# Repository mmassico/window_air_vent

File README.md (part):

# Window vent

A demand-controlled window ventilator for one room. Two 80 mm fans move air through a foam window insert: one brings fresh air in, the other exhausts stale air. A single butterfly-damper housing closes both holes with one shaft, turned by a silent stepper motor. An ESP32 reads a CO₂ sensor and runs the fans and the damper.

There is no heat recovery: every litre of air exhausted is lost heat. In exchange it is simple, cheap and automatic. See the estimates below.

> **Status: prototype, running in a window.** The complete unit is installed in a window, on the controller PCB and the [web application](firmware/README.md#the-web-application-webui), and ventilates on its own from its CO₂ reading. It closes when it's loud outside, using a microphone listening through a tube in the foam. Every printed part has been printed and test-fitted (housing, discs, motor plate, magnet cap, electronics box, tube spacer, louvers), and several were refined from those prints: the shaft holes' sacrificial fins, the box's back tabs, the louvers' snap-in combs, and the discs' seats. The lip seals are installed and tested: with the 1.6 mm neoprene, the closed discs now press evenly on the foam all round, after two rounds of tuning the discs' seats (the housing stayed as printed). The housing was then reprinted with flat shaft bosses and the discs with matching flats: the gap at the bosses is gone (the first, curved bosses left 0.3 to 0.75 mm), and the reprinted electronics box fits too, its back tabs and the notches for the fan's rubber bumpers included; the tabs make mounting it on the housing much easier. The shaft holes' sacrificial fins work as intended: no warping, and they drill out easily. The lip foam cutting guides are printed and tested: cutting the foam with them is much easier, faster and more accurate than with the paper templates. The foam-free `disc_nofoam` is checked in CAD but not tested yet. Its CO₂ reading agrees with a calibrated meter within the sensor's tolerance. What's still to come is time: it has only just gone in, so it hasn't seen a season yet. The geometry is also checked in CAD (closed solids, the discs swing freely, the lips stop them).

## How it works

- **Foam insert.** A block of 2 in (51 mm) XPS foam, 30 psi grade, fills the window gap (100 mm or less, so a child can't fit through). Two 83 mm holes (a 3-1/4 in hole saw, see [drilling](#drilling-the-foam-insert)), stacked vertically: exhaust on top, intake below. The cold incoming air sinks, and the warm exhaust rises, so with the intake low neither one loops straight back into the other, indoors or out. An [insect screen](#insect-screen) in a printed frame covers the outdoor face.
- **Damper housing.** It sits on the **room** face of the foam, so its moving parts stay warm and dry (no ice). Its two spigots fit snugly in the foam holes; two O-rings on each are optional, for a hole that comes out loose. The housing comes out in spring, and the foam insert stays reusable.
- **Butterfly dampers.** One vertical 5 mm steel shaft runs through both ducts and carries a disc in each. A quarter turn opens or closes both. Each disc closes against two half-ring lips lined with thin foam (or bare, with [`disc_nofoam`](#without-lip-foam)), one on each side of the shaft. One lip is flat; the other is a 45° cone, and the half of the disc that closes against it (engraved B) has a matching 45° bevel, so neither prints as a flat overhang.
- **Motor and encoder.** A NEMA 17 pancake stepper on top turns the shaft through a flexible coupler. A TMC2209 driver keeps it silent. The motor screws to a separate plate on the bench, and the plate then screws onto a frame on top of the housing from above. An AS5600 magnetic encoder at the bottom reads the absolute shaft angle, so the firmware always knows whether the dampers are really closed, with no homing and no limit switch.
- **Fans.** Two 80 mm PWM fans screw onto the room end of the housing.
- **Electronics box.** A tray under the housing holds a 5 × 7 cm perfboard with the ESP32 and the TMC2209 soldered on. The encoder plate is its lid, and its front wall rises to close the front of the bottom bay. The cables run down the right side (seen from the room), hidden behind the fans and held by three tie-wrap anchors on the back of the fan plate; the same anchors and a cable entry on the left side allow the mirror image. Power comes from two plug-in adapters: a 12 V brick for the fans and the motor, whose wire comes in with the other cables, and a 5 V USB-C adapter for the ESP32, whose cable passes through a diamond opening in the left wall. The [layout drawing](doc/ebox_layout.svg) shows where everything goes on the perfboard.
- **Water stays out of the room.** A 3 mm drip dam across the lower part of each bore, just before the fan, stops droplets from running indoors. Around the bottom shaft hole in each duct, a 16 mm boss rises 3 mm above the floor, so water flows around it instead of down the shaft. An optional [drip tray](#drip-tray) under the unit, on the window ledge, catches anything that still drips; it evaporates there.
- **How it seals.** The lips do the sealing, not the gap between the disc and the bore: the flat lip is 5.6 mm wide and overlaps the disc edge by 2 mm, and the conical lip meets the disc's bevelled rim over a band about 2.8 mm wide (the same 2 mm across the bore, along the 45° slope). Between them is 1.6 mm neoprene in a gap of about 1.5 mm, so it is only lightly squeezed: the disc's two seats are relieved for it (see [cutting the lip foam](#cutting-the-lip-foam)). The disc is 67 mm in a 74 mm bore so it can be slid in edge-on past the dam and the bosses. Around the shaft, where the lips must stop to clear the hub, a boss at the top and the one at the bottom close the gap. Their inner faces are flat, square to the shaft, and the disc's two shaft ends are cut to matching flats: a flat end turning about the shaft stays in its own plane, so the gap is 0.2 mm at every angle.

## Estimates (one sleeper)

| Airflow (each way) | CO₂ in the room | Heat lost at −20 °C outdoors |
|---|---|---|
| 5 L/s (11 CFM) | ~1000 ppm | ~250 W |
| 8 L/s (17 CFM) | ~800 ppm | ~400 W |
| 11 L/s (23 CFM) | ~700 ppm | ~540 W |

At 8 L/s, roughly 10 hours a day over a cold-climate heating season (about 200 days, electricity at 7–11 ¢/kWh), the lost heat costs about $35–45. The fans use about 1 W each.

## Printed parts

| Part | <div style="width:180px">Thumbnail</div> | Qty | Description | Size (mm) | Print orientation |
|---|:---:|---|---|---|---|
| `body` |  | 1 | Housing: two ducts with the damper lips, drip dams and shaft bosses, spigots for the foam, fan plate, motor frame and encoder plate | 90 × 241 × 114 | Fan plate on the bed, no supports |
| `disc` |  | 2 | Butterfly damper disc, clamped to the shaft by two M3 grub screws; the half engraved B has a 45° bevel on its rim. Its seats are relieved for the 1.6 mm lip foam, and its two shaft ends are cut flat to face the bosses | 67 × 65 × 14 | Plate on the bed, hub up |
| `disc_nofoam` |  | (2) | Instead of `disc`, for lips [without foam](#without-lip-foam): half A is 3.6 mm thick and half B's bevel is smaller, so both seats close to 0.3 mm from the bare lips | 67 × 65 × 14 | Plate on the bed, hub up |
| `motor_plate` |  | 1 | The motor screws to it on the bench; it then sits on top of the housing: two screws in front of the motor, and two tabs at the back, down through the frame and screwed to the tower walls | 56 × 61 × 15 | Top face on the bed, tabs up |
| `magnet_cap` |  | 1 | Holds the encoder magnet on the bottom end of the shaft; one M3 grub screw, height adjustable ±1 mm | 14 × 14 × 12 | Bore down |
| `ebox` |  | 1 | Electronics box under the housing; its front wall also covers the front of the bottom bay, and two back tabs screw to the bay walls | 80 × 76 × 64 | Floor on the bed |
| `tube_spacer` |  | 1 | Flat "8" over both spigots, against the stop rings and squeezed by the foam: it holds the spigots' ends at their spacing, so foam holes slightly off 96 mm can't bend the ducts and bind the shaft. The vent sits 2.5 mm further out of the foam | 90 × 186 × 2.5 | Flat |
| `screen_frame` |  | 1 | [Insect screen](#insect-screen) frame on the foam's outdoor face: the mesh is pressed into a groove around both holes, two sleeves plug into the holes, four screws in the corners, a drain at the bottom of each hole | 94 × 193 × 15 | Outdoor face on the bed, sleeves up |
| `tray` |  | (1) | Optional [drip tray](#drip-tray) on the window ledge, under the whole unit: the electronics box stands on ribs above its floor, and an adjustable leg in each corner levels it | 112 × 115 × 22 | Floor on the bed |
| `tray_feet` |  | (4) | The tray's feet, one per leg: each slides in its post's socket, carries a captive M3 nut, and has a groove for the M2 stop | 9 × 9 × 20 each | On its side, the nut's slot up |

**Housing and discs must match.** The housing's shaft bosses have flat inner faces, and the discs have matching flats. A housing printed before this change (curved boss faces) needs the earlier discs: set `flat_boss = false` in `cad/window_vent.scad` and export `disc` (or `disc_nofoam`). A disc with flats leaves a 1.6 mm gap at a curved boss, and a disc without them won't turn between flat bosses.

**For a 180 mm printer** (e.g. Bambu Lab A1 mini), print the housing in two halves instead of `body`. The cut runs midway between the two ducts, where only the fan plate joins them; a small splice plate behind the fan plate joins the halves again with four M3 screws, driven from the fan side in the band between the two fans. Each half prints like the full housing, in about half the time (roughly 5–6 h), so they can go on different days; use the same spool and profile for both.

| Part | <div style="width:180px">Thumbnail</div> | Qty | Description | Size (mm) | Print orientation |
|---|:---:|---|---|---|---|
| `body_top` |  | 1 | Upper half: exhaust duct, upper fan, motor frame, and both middle tie-wrap anchors (whole) | 90 × 130 × 114 | Fan plate on the bed, no supports |
| `body_bottom` |  | 1 | Lower half: intake duct, lower fan, encoder plate; notched under the two middle anchors | 90 × 116 × 114 | Fan plate on the bed, no supports |
| `splice` |  | 1 | Joins the halves behind the fan plate; four M3 nut pockets on its back | 60 × 32 × 6 | Flat, nut pockets up |

**Optional test prints, before the housing.** Print the small real parts first (discs, motor plate, magnet cap, about 1.5–2 h): they test the rod, the grub screws, the motor and the magnet. Then:

| Part | <div style="width:180px">Thumbnail</div> | Size (mm) | Time | What it tests |
|---|:---:|---|---|---|
| `fittest` |  | 60 × 34 × 22 | about 20–30 min | The housing's printer-sensitive features, in its print orientation, engraved A to G (see below) |
| `oring_test` |  | Ø 90 × 18 | about 30 min | One spigot section (with an O-ring groove): push it into a test hole cut in a foam scrap, bare first; if it's loose, try it with an O-ring |

**The fit-test coupon.** It copies seven features of the housing that depend most on the printer: holes and a slot, a nut pocket, a pilot for self-tapping screws, the conical lip's 45° ledge and a countersink. Each is engraved with a letter, A to G. Print it with the housing's filament and settings, then check each feature against the table below: if one fails, adjust the slicer (or the hole sizes in the model) before starting the 9–12 hour housing print.

| | Feature | Copied from | Pass if |
|---|---|---|---|
| A | M3 hole + nut pocket | fan plate | the nut drops in and stays; an M3 screw passes freely |
| B | Ø 2.5 self-tapping pilot | the box cover bosses | an M3 screw cuts a firm thread without splitting the post |
| C | 5.6 mm ledge with a 45° underside (on the back of the plate) | conical lip B in each bore | the slope is smooth, not drooping or stringy |
| D | Ø 5.4 shaft hole, horizontal, with its sacrificial fin | bearing holes in the duct walls | the top of the hole stays round; after drilling the fin out (see below), the 5 mm rod turns freely |
| E | AS5600 diagonal slot (3.5 wide) on a 2 mm standoff | encoder plate | an M3 screw passes at both ends of the slot |
| F | M3 hole, horizontal | motor frame | an M3 screw passes freely |
| G | M3 hole with a 90° countersink, opening on the bed | split housing joint (`body_top` and `body_bottom`) | an M3 flat-head screw sits flush or just below the surface |

PETG. No support is needed anywhere: every face that looks down when printing (the lip B seat, the disc bevel, the boss sides, the O-ring grooves, the countersinks) slopes at 45° or less.

### Filament

About **0.5 kg of PETG** for one unit (about half a 1 kg spool), or roughly $12–17 at $25–35/kg.

| Part | Qty | Solid volume |
|---|---|---|
| `body` | 1 | 282 cm³ |
| `disc` | 2 | 2 × 12.7 = 25 cm³ (`disc_nofoam`: 2 × 14.7) |
| `motor_plate` | 1 | 12.6 cm³ |
| `magnet_cap` | 1 | 1.6 cm³ |
| `ebox` | 1 | 47 cm³ |
| `tube_spacer` | 1 | 4.5 cm³ |
| `screen_frame` | 1 | 39 cm³ |
| **Total** | | **≈ 412 cm³** |

The split housing (`body_top` 136 cm³, `body_bottom` 145 cm³, `splice` 8 cm³) adds about 7 cm³ (9 g).

- Printed fully solid, 412 cm³ of PETG (1.27 g/cm³) weighs about 523 g.
- Infill hardly matters: almost every wall, plate, lip and disc is 6 mm thick or less, so with 4–6 perimeters the slicer prints it solid anyway. Expect about 470–520 g, plus a little for the skirt or brim and purging.
- The optional test prints add about 35 cm³ (44 g): `fittest` 12 cm³, `oring_test` 20 cm³, `fin_test` 3 cm³. The optional `drill_guide` adds 9 cm³ (11 g), and the optional lip foam cutting guides 9 cm³ (12 g): `foam_guide_a` 4.3 cm³, `foam_guide_b` 5.0 cm³. The screen frame's `screen_test` adds 6 cm³ (7 g). The optional drip tray adds 46 cm³ (58 g): `tray` 41 cm³, `tray_feet` 5 cm³, and its `tray_test` 5 cm³ (6 g).
- Print time: very roughly 9–12 hours for the housing on a Bambu Lab P1 (0.2 mm layers; about 7–9 hours at 0.28 mm), and about 3–4 hours for all the other parts together. The slicer gives the exact figures.

### Slicer settings

Most parts are thin, so the number of walls (Bambu Studio: Strength → **Wall loops**) matters more than the infill percentage: with enough walls, the thin parts come out solid and the infill only fills the few thicker zones.

| Part | Wall loops | Sparse infill | Why |
|---|---|---|---|
| `body` (or `body_top` and `body_bottom`) | 4 | 25 % | Thin walls everywhere; the infill only reaches the thick zones (bosses, spigot roots, fan plate). No supports: a sacrificial fin holds up the top of each of its four shaft holes (see below) |
| `disc` (or `disc_nofoam`) | 5 | 40 % | The grub screws thread into the hub: 5 loops leave about 2 mm of solid plastic around each hole |
| `motor_plate` | 5 | 40 % | Screw holes, bosses and tabs under clamping load |
| `magnet_cap` | | 100 % | Tiny, with a grub screw in it: print it solid |
| `splice` | 5 | 40 % | Joins the two halves: nut pockets and countersunk screws |
| `ebox` | 4 | 15–20 % | No real loads; a 4th wall (same print time) makes the walls around the screw holes stronger |
| `tube_spacer` | | 100 % | Thin rings (3 mm wide, 2.5 mm thick) that must not stretch: print it solid |
| `screen_frame`, `screen_test` | 4 | 25 % | Thin plate and sleeves: 4 walls print them nearly solid, so the groove's walls hold the spline |
| `tray`, `tray_feet`, `tray_test` | 4 | 25 % | The 5 bottom layers below keep the tray's 1.6 mm floor watertight; 4 walls make the posts and feet nearly solid |
| `fittest`, `oring_test` | 4 | 25 % | As the housing, so they test what the housing will be |
| `drill_guide` | 4 | 40 % | Small; 4 walls make the bushings solid |
| `foam_guide_a`, `foam_guide_b` | 4 | 40 % | Thin plate and rib: 4 walls print them solid, so they stay flat and stiff |
| `louver_chassis` | 3 | 20 % | Light load |
| `louver_blade` | 3 | 15 % | Thin and light; their pins come out solid anyway |
| `louver_link_nopad` (or `louver_link`), `louver_retainer` | | 100 % | Small and thin |
| `fan_spacer` | 3 | 15 % | Thin vertical walls and vanes: 3 walls print them solid |
| `fan_shim` | | 100 % | Thin sheet, 1.25 mm: print it solid, at a layer height that gives that thickness |
| `fan_gasket_template` | 3 | 15 % | Just a template |

- **Infill pattern: gyroid.** Equally strong in every direction, and it prints smoothly in PETG.
- **Top and bottom shell layers: 5.** Flat faces stay smooth and the infill doesn't show through.
- **Supports: none.** Every part is designed to print without them. The housing's four shaft holes print horizontal, so each one carries a sacrificial fin: a thin lattice of X's (0.8 mm, two nozzle lines; `fin_t` in the model, 0 for none) standing on the bottom of the hole and holding up its top, with 1.5 mm clear at each end. After printing, drill the fins out by hand with a 5.2 mm bit (13/64 in, the one used on the housing; 5.4 or 5.5 mm also works): the bit enters the clear end first, sits square, and cuts the fin easily. Tested on the housing: the holes come out round, with no warping, and the 5 mm rod turns freely. Feature D of `fittest` is the same hole with the same fin, and `fin_test` is a 10-minute block with two of them.

## Hardware

Prices: Amazon.ca, October 2026, before taxes. Packs of two leave a spare.

| Item | Qty | Notes | Price (CAD) |
|---|---|---|---|
| 80 mm PWM fan, ≥ 2 mm H₂O static pressure | 2 | Noctua NF-A8 PWM (2.37 mm H₂O, 17.7 dB(A) max). Run at 30–60% | 2 × $24.95 |
| Stepper motor, NEMA 17 pancake | 1 | StepperOnline 17HS08-1004S (42 × 42 × 20 mm, 5 mm shaft, 13 N·cm). Any NEMA 17 fits the mount | $26.50 |
| TMC2209 stepper driver | 1 | StealthChop for silent moves; UART for StallGuard | $16.99 (pack of 2) |
| AS5600 magnetic encoder board + **diametric** magnet | 1 | Sold with the magnet (the kit: 23.3 × 22.8 mm board, 3.95 × 2 mm magnet). A 20 × 20 board with 15 mm hole spacing also fits: 4 × M3 × 12 + nuts onto standoff pads on the bottom plate. See the magnet note below | $12.69 (pack of 2) |
| ESP32-S3 dev board | 1 | An ESP32-S3-N16R8 board in the DevKitC-1 layout (2 × 22 pins) with a U.FL connector and an external antenna, for the v2.0 PCB; or the Freenove ESP32-S3-WROOM Lite (FNK0099), the board the firmware's pinout was first written for, which also fits the v2.0 PCB on its 20 inner pins of each row. Other ESP32-S3-WROOM-1 boards work with a pin check. Flash it over USB on the bench; the final firmware updates over Wi-Fi | — |
| CO₂ sensor, NDIR | 1 | Sensirion SCD40 module (CO₂ + temperature + humidity, I²C). Not CCS811/SGP30 ("eCO₂" estimates) | $37.45 |
| DS18B20 temperature probe, waterproof | 1 (+1 optional) | Outdoor air: the 6 mm stainless probe on its cable goes through the foam insert ([template](#drilling-the-foam-insert)); if possible, far from the exhaust (the upper hole), whose warm air skews the reading. A second one, indoors on an inside wall, is optional: the SCD40 already reads the room's temperature | — |
| Steel rod, 5 mm × 200 mm | 1 | Damper shaft. 200 mm fits as is, no cutting. If it is HSS (very hard), grind a small flat with a rotary tool where each disc and the coupler clamp, so the screws can't slip | $12.79 (pack of 2) |
| Flexible shaft coupler, 5–5 mm, 19 × 25 mm | 1 | | $13.49 (pack of 2) |
| M3 × 35 screws + M3 nuts | 8 each | Fans. Two stacked fans per duct ([optional](#optional-two-fans-per-duct-with-a-spacer)): M3 × 75 with the `fan_spacer` and its shims, M3 × 60 without | — |
| M3 × 8 screws | 4 | Motor to motor plate, through the bosses under the plate. Not longer: the motor's holes are only 2.5 mm deep ([section](doc/motor_mount.svg)) | — |
| M3 × 10 (or M3 × 12) screws + M3 nuts | 6 each | Motor plate: two through the frame in front of the motor, two through the tower walls and the plate's back tabs. Electronics box: two through the bay walls and the box's back tabs | — |
| M3 grub screws, 6 mm (and one 4–5 mm) | 5 | Two 6 mm per disc, 24 mm apart along the hub, so the disc can't rock on the shaft (flush with the hub); one 4–5 mm in the magnet cap (a 6 mm one would stick out 1.5 mm). Self-tapping into the plastic | — |
| O-rings, 74 × 3 mm, nitrile 70A | 4 | Optional, and not needed by default: the plain Ø 83.7 spigots are a snug fit in the hole (83.3 mm with the 3-1/4 in hole saw). For a hole that comes out loose, set `orings = true` before printing the housing: two grooves per spigot, sized for this O-ring (about 6% stretch, 20% squeeze in an 83.3 mm hole) | $12.79 (pack of 10) |
| Insect screen kit: fibreglass mesh, 0.125 in screen spline, spline roller | 1 | [Insect screen](#insect-screen): a piece of mesh about 115 × 210 mm and about 50 cm of spline (or 3 mm O-ring cord, cut from the 74 × 3 O-rings above) | — |
| Countersunk screws, 8 mm head (3.5 mm high), about 25 mm long | 4 | Screen frame into the foam (4.25 mm holes) | — |
| M3 × 20 button head screws (ISO 7380, 2 mm hex) + M3 nuts | 4 each | Optional [drip tray](#drip-tray): the legs. Felt pads under the feet are optional too | — |
| M2 × 6 flat head screws | 4 | Optional [drip tray](#drip-tray): the legs' stops, through each post's outer wall (self-tapping) | — |
| XPS foam board, 2 in (51 mm), 30 psi | 1 | Foam insert, e.g. Owens Corning FOAMULAR C-300 (2 × 24 × 96 in, R-10). The 30 psi grade over the 20 psi (wall) one: stiffer under the housing's weight, it doesn't creep around the spigots, and the hole saw cuts it cleaner. Many boards have shiplap (SL) edges, stepped to overlap on a wall: cut the insert from the middle of the board, or saw the step off any edge that meets the window frame | — |
| Closed-cell neoprene foam sheet, self-adhesive, 1/16 in (1.6 mm) | 1 | Lip seals, cut with the [templates](#cutting-the-lip-foam); not needed with `disc_nofoam` ([without lip foam](#without-lip-foam)). The model leaves a 1.5 mm gap, so the foam is only lightly squeezed: closed-cell neoprene is too stiff for more | |
| Perfboard (protoboard), 5 × 7 cm, holes 66 × 46 mm | 1 | Carrier for the ESP32 and the TMC2209 in the electronics box | |
| Resistors and capacitor for the perfboard | | 1 kΩ (TMC2209 UART), 10 kΩ × 5 (driver enable pull-up, two fan PWM pull-downs, two tach pull-ups), 100 kΩ + 22 kΩ (12 V sense), 4.7 kΩ (DS18B20 pull-up; × 2 with the optional indoor sensor), 100 µF ≥ 25 V electrolytic (TMC2209 motor supply). See [firmware/README.md](firmware/README.md) | — |
| Female pin headers, 2.54 mm (optional) | to suit | Sockets for the ESP32 and the TMC2209 instead of soldering them, so they unplug for replacement (`esp_mount`, `tmc_mount`; the box has room for both) | |
| M2 screws, about 6 mm | 4 | Perfboard onto the box standoffs (self-tapping) | |
| M3 × 12 countersunk (flat head, ISO 10642 or DIN 965) screws + M3 nuts | 4 each | Split housing only: fan plate to the splice, heads flush in 90° countersinks | — |
| M3 × 12 screws | 2 | Electronics box: through the front cover (self-tapping) | — |
| Small tie wraps, 2.5–3.6 mm | 3+ | Cable anchors (three on each side; use one side) | |
| 12 V power brick | 1 | Fans and motor, about 1 A. Only its wire enters the box, to a 2-pin screw terminal on the perfboard | — |
| USB-C power adapter, 5 V (1 A or more), and a USB-C cable | 1 | Powers the ESP32 through its USB-UART connector, which also gives the console. The cable passes through a diamond opening in the box's left or right wall (`usb_port`: or only a cross to drill, or nothing; `usb_side`: left, right or both) | — |
| **Total bought** | | Not counting the foam insert and foam sheet, or the two power adapters | **≈ $181** |

### The stepper motor

The StepperOnline 17HS08-1004S, from its sheet and checked with a caliper. Its M3 holes are only 2.5 mm deep, so the motor plate has a 2 mm boss under each screw hole: through the 4 mm plate and the boss, an M3 × 8 reaches 2 mm into the motor. The bosses and the screw heads sit in the frame's diamond pockets.

Its four leads, from the sheet, and where they go on the controller PCB's motor header J4 (silkscreen 1A, 1B, 2A, 2B; the TMC2209's M1A, M1B, M2A, M2B). Each coil is a pair: about 3.7 Ω between its two leads, nothing between the pairs, which an ohmmeter confirms before plugging in.

| J4 pin | Silkscreen | Driver output | Lead | Coil |
|---|---|---|---|---|
| 1 (square pad) | 1A | M1A | Black | A |
| 2 | 1B | M1B | Green | A\ |
| 3 | 2A | M2A | Red | B |
| 4 | 2B | M2B | Blue | B\ |

If the motor turns the wrong way, swap the two leads of one coil (black and green, for example). Never plug or unplug the motor with 12 V on: it can destroy the driver.

### The AS5600 board, a magnetic rotary position sensor

The kit board, measured. Its four mounting holes form a 16.7 × 16.2 mm rectangle (not a square); the diagonal slots in the encoder plate take it as well as the smaller 20 × 20 boards. Mount it chip up, under the magnet, and solder the wires straight into its holes: they run inward under the board, in the 2 mm the standoff pads leave, and down through the diamond window under the chip.

### The ESP32-S3 board, the Wi-Fi microcontroller

The Freenove ESP32-S3-WROOM Lite, measured. Its two pin rows are 25.3 mm apart, so they land 10 holes apart on the perfboard. It has two USB-C connectors at one end: plug the cable into the USB-UART one (power and console). The module's antenna sticks out 7 mm beyond the other end.

### The TMC2209 module, a silent stepper motor driver

A StepStick-format driver, measured: 20.81 × 15.08 mm, two rows of 8 pins 12.7 mm apart (5 holes on the perfboard). The chip is on the underside; its heatsink (15 × 14.4 mm, fins along the pin rows) sticks onto the thermal pad on top, toward the DIR/GND end so it clears the potentiometer, and stands 14.70 mm from the board's underside.

Check which pin carries the chip's UART. Some modules, such as the TMC2209-LA, have a 0 Ω link that routes it to either the PDN pin (pin 4) or the UART pin (pin 5), and come with it on PDN; the controller uses both. On the PCB, since v1.3, two 0 Ω 0402 jumpers on the back, JP3 (pin 4) and JP4 (pin 5), put the UART line on both pins, so either kind works; leave one out if a module uses that pin for something else. On an older PCB or the perfboard, nothing else uses pin 4, so a short wire between pins 4 and 5 on the board's underside does the same (the firmware README's bring-up, step 5, shows how to tell).

### The SCD40 board, the CO₂ sensor

The Sensirion SCD40 on a small 13.70 × 21.70 mm board, measured: 7.85 mm from its underside to the sensor's top, four pin holes 2.54 mm apart along the bottom edge (GND, VDD, SCL, SDA). It carries its own I²C pull-ups (R1, R2, 10 kΩ), so the controller needs none for it. On the controller PCB, J5 has the same pin order, so a straight 4-wire cable joins them. Keep the sensor's membrane uncovered (see the warning below).

> [!WARNING]
> **SCD40: do not remove the white membrane on top of the sensor.** It looks like a small sticker, but it is part of the sensor: a gas-permeable filter that lets ambient air reach the photoacoustic NDIR cell while keeping dust, splashes and other contaminants out. Do not press on it, cover it, or clean near it with solvents or compressed air.

### The MAX9814 board, the microphone (optional)

For the [audio mode](firmware/README.md#wiring), measured: 25.6 × 14.3 × 1.62 mm, 9 mm from its underside to the capsule's top, and parts up to about 3 mm on the back. The 9.70 mm capsule sits 2.10 mm from one end, centred across the board; the five header holes (GND, Vdd, Gain, Out, AR) run along the other end, and two mounting holes flank the capsule. Tie Gain to Vdd (40 dB) and leave AR open. It lies capsule down in the [microphone tube](window_insert/README.md#outdoor-microphone).

### The electronics box layout

The box seen from above, to scale, with the room at the bottom. The ESP32 lies across the back half, its pins soldered on the perfboard's grid, with its USB-end pins one column in from the board's edge so they clear the corner standoff; the TMC2209 sits at the front right, next to the 12 V terminal and the cable entry. The ESP32 can also be turned 180° in the same place, USB end toward the right wall: the box has a diamond opening on each side (views `ebox_elec` and `ebox_elec_alt` in the model). Keep wires and copper away from the antenna's end.

### Firmware

The ESP32 runs Arduino sketches (esp32 core 3.x). The first, [`firmware/baremetal/`](firmware/baremetal), is a serial command console that tests each electronic part on its own: fans, motor and driver, encoder, CO₂ sensor, temperature probes and the 12 V supply, and optionally a microphone's sound level (audio mode). The second, [`firmware/webui/`](firmware/webui), is the application: the CO₂ control, with its own web page on the home network for the live readings, graphs, settings and manual control, and a simulation that stands in for the sensors until they're connected. Both compile cleanly, and the web application runs on the bare ESP32 board in simulation, and the bare-metal console has now checked every part on the bench. [firmware/README.md](firmware/README.md) has the board settings, the [wiring diagram](firmware/images/wiring.svg), a part-by-part bring-up, the command list and the web application.

**Building the perfboard.** The [build plan](doc/perfboard.svg) puts this wiring on the 5 × 7 cm protoboard: the ESP32-S3 and the TMC2209 on their grid positions in the box, the headers, resistors, capacitor and 12 V terminal around them, and 61 numbered wires on the underside, each listed with both of its holes. A [PDF version](doc/perfboard.pdf) splits it over three landscape Letter pages for the bench: the component side, the solder side and the wire list. Solder the parts and the wires that run under the modules first, then the two modules.

<p align="center">
  
</p>

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
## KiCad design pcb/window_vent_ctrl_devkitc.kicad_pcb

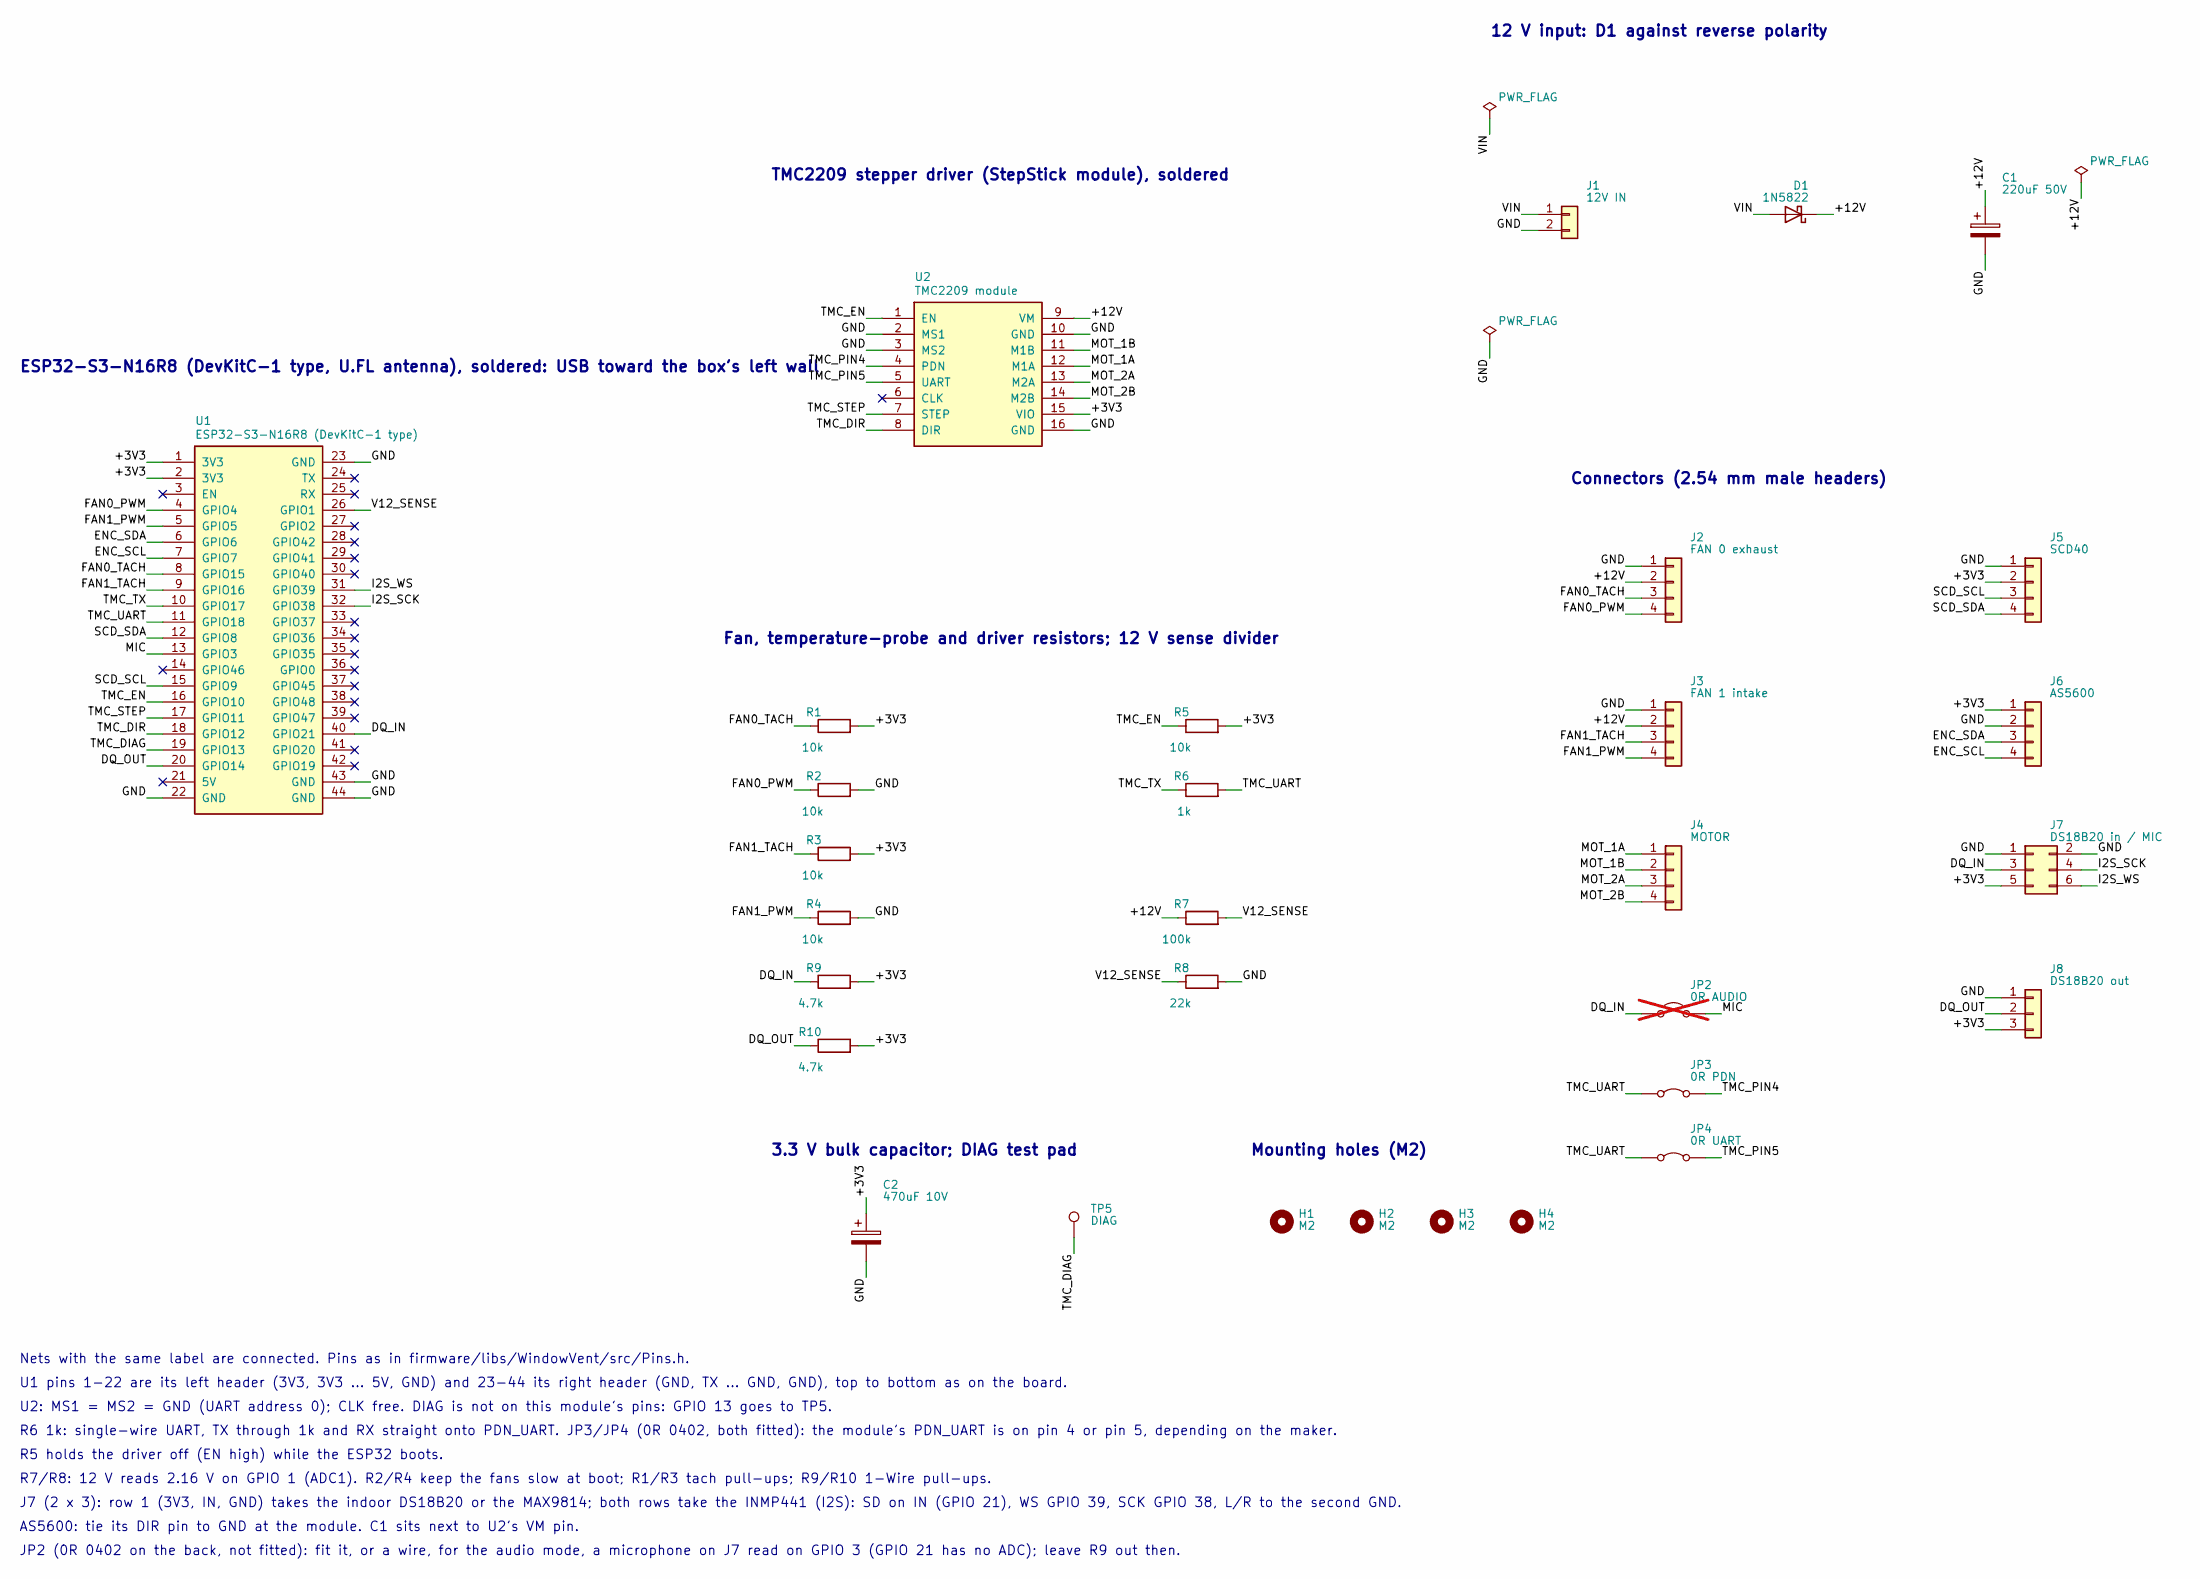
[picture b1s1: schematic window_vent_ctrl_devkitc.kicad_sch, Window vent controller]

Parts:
C1: 220uF 50V; CP_Radial_D10.0mm_P5.00mm
C2: 470uF 10V; CP_Radial_D6.3mm_P2.50mm
D1: 1N5822; D_DO-201AD_P5.08mm_Vertical_AnodeUp_Tight
H1, H2, H3, H4: M2; MountingHole_2.2mm_M2
J1: 12V IN; PinHeader_1x02_P2.54mm_Vertical
J2: FAN 0 exhaust; PinHeader_1x04_P2.54mm_Vertical
J3: FAN 1 intake; PinHeader_1x04_P2.54mm_Vertical
J4: MOTOR; PinHeader_1x04_P2.54mm_Vertical
J5: SCD40; PinHeader_1x04_P2.54mm_Vertical
J6: AS5600; PinHeader_1x04_P2.54mm_Vertical
J7: DS18B20 in / MIC; PinHeader_2x03_P2.54mm_Vertical
J8: DS18B20 out; PinHeader_1x03_P2.54mm_Vertical
JP2: 0R AUDIO; R_0402_1005Metric_Pad0.72x0.64mm_HandSolder; not fitted
JP3: 0R PDN; R_0402_1005Metric_Pad0.72x0.64mm_HandSolder
JP4: 0R UART; R_0402_1005Metric_Pad0.72x0.64mm_HandSolder
R1, R2, R3, R4: 10k; R_Axial_DIN0207_L6.3mm_D2.5mm_P2.54mm_Vertical
R5: 10k; R_DIN0207_P10.16mm_Flat_Tight
R6: 1k; R_DIN0207_P10.16mm_Flat_Tight
R7: 100k; R_DIN0207_P10.16mm_Flat_Tight
R8: 22k; R_DIN0207_P10.16mm_Flat_Tight
R9, R10: 4.7k; R_DIN0207_P10.16mm_Flat_Tight
TP5: DIAG; TestPoint_THTPad_D2.0mm_Drill1.0mm
U1: ESP32-S3-N16R8 (DevKitC-1 type); ESP32S3_DevKitC_N16R8
U2: TMC2209 module; TMC2209_StepStick

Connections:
/+3V3: C2.1, J5.2, J6.1, J7.5, J8.3, R1.2, R3.2, R5.2, R9.2, R10.2, U1.1 (3V3), U1.2 (3V3), U2.15 (VIO)
/+12V: C1.1, D1.1 (K), J2.2, J3.2, R7.1, U2.9 (VM)
/DQ_IN: J7.3, JP2.1 (A), R9.1, U1.40 (GPIO21)
/DQ_OUT: J8.2, R10.1, U1.20 (GPIO14)
/ENC_SCL: J6.4, U1.7 (GPIO7)
/ENC_SDA: J6.3, U1.6 (GPIO6)
/FAN0_PWM: J2.4, R2.1, U1.4 (GPIO4)
/FAN0_TACH: J2.3, R1.1, U1.8 (GPIO15)
/FAN1_PWM: J3.4, R4.1, U1.5 (GPIO5)
/FAN1_TACH: J3.3, R3.1, U1.9 (GPIO16)
/GND: C1.2, C2.2, J1.2, J2.1, J3.1, J5.1, J6.2, J7.1, J7.2, J8.1, R2.2, R4.2, R8.2, U1.22 (GND), U1.23 (GND), U1.43 (GND), U1.44 (GND), U2.2 (MS1), U2.3 (MS2), U2.10 (GND), U2.16 (GND)
/I2S_SCK: J7.4, U1.32 (GPIO38)
/I2S_WS: J7.6, U1.31 (GPIO39)
/MIC: JP2.2 (B), U1.13 (GPIO3)
/MOT_1A: J4.1, U2.12 (M1A)
/MOT_1B: J4.2, U2.11 (M1B)
/MOT_2A: J4.3, U2.13 (M2A)
/MOT_2B: J4.4, U2.14 (M2B)
/SCD_SCL: J5.3, U1.15 (GPIO9)
/SCD_SDA: J5.4, U1.12 (GPIO8)
/TMC_DIAG: TP5.1, U1.19 (GPIO13)
/TMC_DIR: U1.18 (GPIO12), U2.8 (DIR)
/TMC_EN: R5.1, U1.16 (GPIO10), U2.1 (EN)
/TMC_PIN4: JP3.2 (B), U2.4 (PDN)
/TMC_PIN5: JP4.2 (B), U2.5 (UART)
/TMC_STEP: U1.17 (GPIO11), U2.7 (STEP)
/TMC_TX: R6.1, U1.10 (GPIO17)
/TMC_UART: JP3.1 (A), JP4.1 (A), R6.2, U1.11 (GPIO18)
/V12_SENSE: R7.2, R8.1, U1.26 (GPIO1)
/VIN: D1.2 (A), J1.1

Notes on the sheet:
ESP32-S3-N16R8 (DevKitC-1 type, U.FL antenna), soldered: USB toward the box's left wall
TMC2209 stepper driver (StepStick module), soldered
12 V input: D1 against reverse polarity
Connectors (2.54 mm male headers)
Fan, temperature-probe and driver resistors; 12 V sense divider
3.3 V bulk capacitor; DIAG test pad
Mounting holes (M2)
Nets with the same label are connected. Pins as in firmware/libs/WindowVent/src/Pins.h.
U1 pins 1-22 are its left header (3V3, 3V3 ... 5V, GND) and 23-44 its right header (GND, TX ... GND, GND), top to bottom as on the board.
U2: MS1 = MS2 = GND (UART address 0); CLK free. DIAG is not on this module's pins: GPIO 13 goes to TP5.
R6 1k: single-wire UART, TX through 1k and RX straight onto PDN_UART. JP3/JP4 (0R 0402, both fitted): the module's PDN_UART is on pin 4 or pin 5, depending on the maker.
R5 holds the driver off (EN high) while the ESP32 boots.
R7/R8: 12 V reads 2.16 V on GPIO 1 (ADC1). R2/R4 keep the fans slow at boot; R1/R3 tach pull-ups; R9/R10 1-Wire pull-ups.
J7 (2 x 3): row 1 (3V3, IN, GND) takes the indoor DS18B20 or the MAX9814; both rows take the INMP441 (I2S): SD on IN (GPIO 21), WS GPIO 39, SCK GPIO 38, L/R to the second GND.
AS5600: tie its DIR pin to GND at the module. C1 sits next to U2's VM pin.
JP2 (0R 0402 on the back, not fitted): fit it, or a wire, for the audio mode, a microphone on J7 read on GPIO 3 (GPIO 21 has no ADC); leave R9 out then.

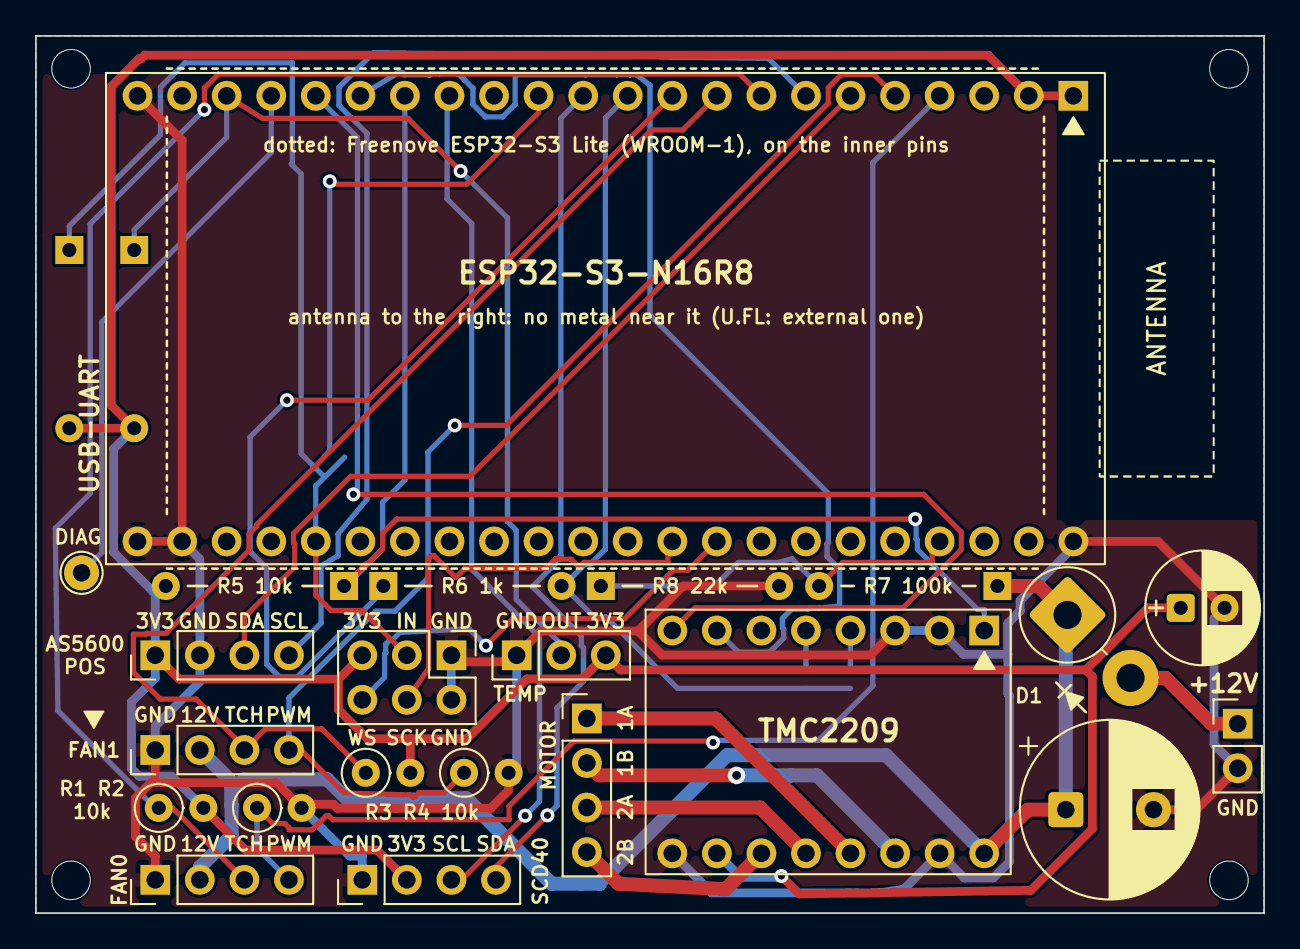
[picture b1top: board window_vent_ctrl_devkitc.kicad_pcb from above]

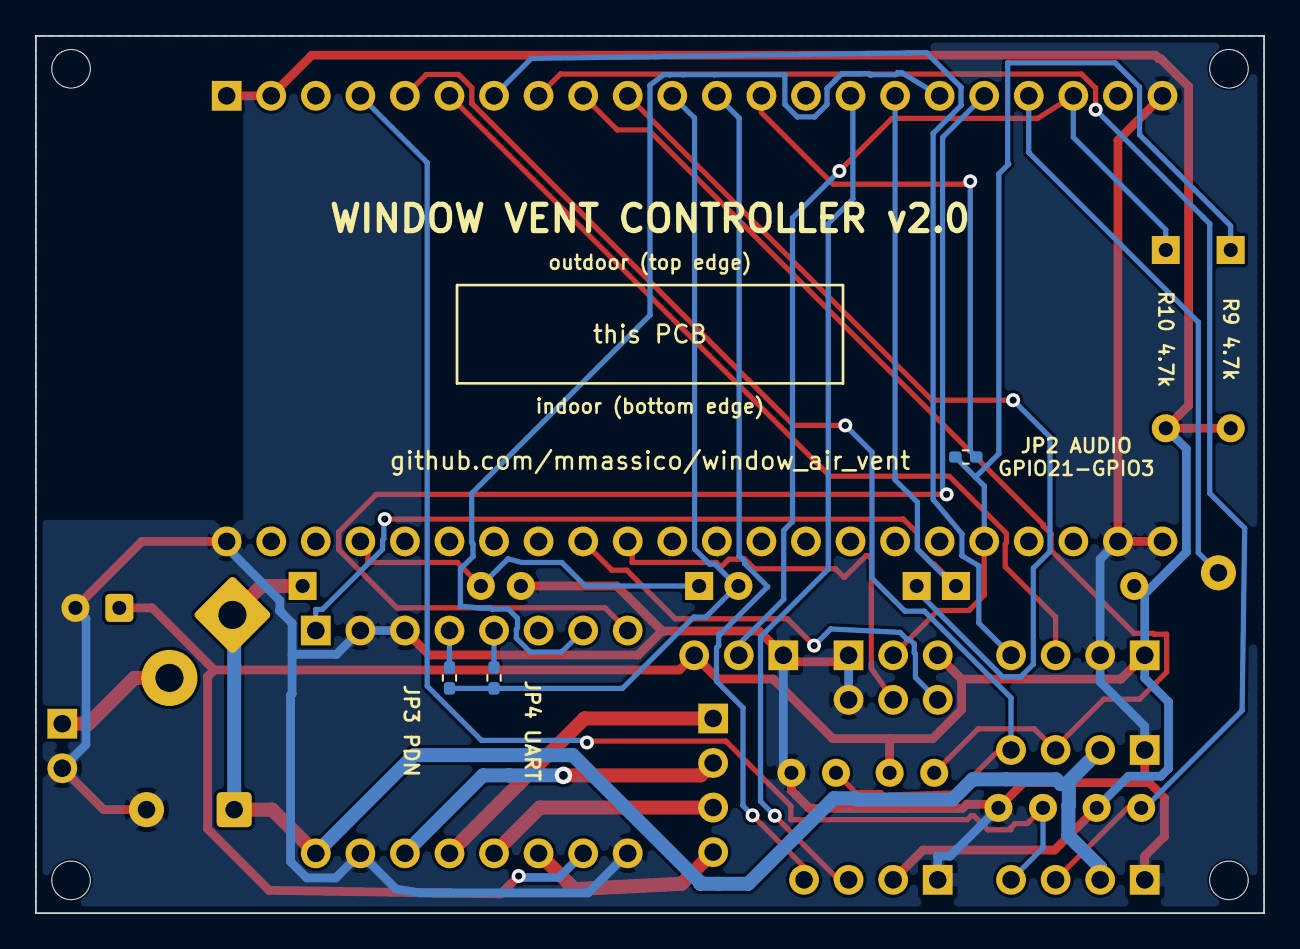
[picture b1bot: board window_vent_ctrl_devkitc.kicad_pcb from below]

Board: 2 copper layers, 70.0 x 50.0 mm, 31 parts (5 on the bottom side), 30 nets.

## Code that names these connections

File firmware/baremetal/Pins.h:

// Pin assignment for the Freenove ESP32-S3-WROOM Lite board (FNK0099).
//
// Avoided: strapping pins (0, 3, 45, 46; 3 only carries the microphone in audio mode), native USB (19, 20),
// octal PSRAM (35, 36, 37) and the console UART (43 TX, 44 RX, through the board's CH343 USB-UART port).
#pragma once

// Console: UART0 on GPIO 43/44 (the USB-UART connector, "onboard code uploader"), 115200 baud.
#define CONSOLE_BAUD    115200

// I2C bus 0: SCD40 CO2 sensor, on a 1-2 m cable, so kept slow.
#define PIN_SCD_SDA     8
#define PIN_SCD_SCL     9
#define SCD_I2C_HZ      100000

// I2C bus 1: AS5600 encoder, local, on its own bus so a sensor cable fault cannot block it.
#define PIN_ENC_SDA     6
#define PIN_ENC_SCL     7
#define ENC_I2C_HZ      400000

// TMC2209 stepper driver.
//   EN is active low; a 10 k pull-up to 3.3 V keeps the motor off until the firmware enables it.
//   UART is single-wire: 1 k from TX to PDN_UART, RX straight to PDN_UART. MS1 = MS2 = GND (address 0).
#define PIN_TMC_EN      10
#define PIN_TMC_STEP    11
#define PIN_TMC_DIR     12
#define PIN_TMC_DIAG    13
#define PIN_TMC_TX      17
#define PIN_TMC_RX      18
#define TMC_UART_BAUD   115200
#define TMC_ADDR        0
#define TMC_RSENSE      0.11f   // ohms, the usual value on StepStick-style modules

// 80 mm 4-wire PWM fans (index 0 = intake, 1 = exhaust).
//   PWM: 25 kHz, 10 k pull-down so the fans stay slow while the ESP32 boots.
//   Tach: open collector, 2 pulses per turn, 10 k pull-up to 3.3 V.
#define PIN_FAN0_PWM    4
#define PIN_FAN1_PWM    5
#define PIN_FAN0_TACH   15
#define PIN_FAN1_TACH   16
#define FAN_PWM_HZ      25000
#define FAN_PWM_INVERT  0       // set to 1 if the PWM line goes through an inverting transistor

// 12 V supply sense: 100 k (top) / 22 k (bottom) divider into an ADC1 pin (ADC2 is unusable with WiFi).
#define PIN_12V_SENSE   1
#define V12_DIV_TOP     100.0f
#define V12_DIV_BOTTOM  22.0f

// DS18B20 temperature sensors (1-Wire), one per pin so each is known by its pin. Three wires each (no parasite
// power), 4.7 k pull-up to 3.3 V per pin at the ESP32 end. Read with the 'temp' command (Ds18b20.cpp).
#define PIN_TEMP_OUT    14      // outdoor: waterproof probe through the foam insert, near the intake, in the shade
#define PIN_TEMP_IN     21      // indoor, optional (the SCD40 also reads room temperature): on an inside wall at
                                // about 1.2-1.5 m, away from the window and heaters; not in audio mode (below)

// Audio mode (optional): an analog microphone module (MAX9814: 3V3, OUT, GND) on the indoor DS18B20's header (J7)
// instead of the probe, to measure the outdoor sound level. That header's line is GPIO 21, which has no ADC, so a wire
// on the PCB joins GPIO 21 to GPIO 3 (ADC1 channel 2, the only free ADC1 pin). GPIO 3 is a strapping pin, but only for
// the JTAG source, and only if an eFuse says so: the mic's bias at reset is harmless. Leave out J7's 4.7 k pull-up
// (R9): it would pull the mic's output toward 3.3 V. The firmware leaves GPIO 21 disconnected (input off, no pulls),
// and the indoor DS18B20 is unavailable. 1 = audio mode, 0 = indoor DS18B20 on GPIO 21.
#ifndef AUDIO_MODE                      // (or -DAUDIO_MODE=1 on the compiler's command line)
#define AUDIO_MODE      0
#endif
#define PIN_MIC         3
#define PIN_MIC_LINK    21      // wired to PIN_MIC, kept high impedance
#define MIC_CAL_DB      0.0f    // dB SPL = dBFS + this ('sound cal' measures it); 0 = uncalibrated, levels in dBFS

// On-board indicators.
#define PIN_LED         2       // blue LED, used as a heartbeat
#define PIN_RGB         48      // WS2812

// Reserved for the INMP441 microphone (I2S) later: SCK 38, WS 39, SD 40.

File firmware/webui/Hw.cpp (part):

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
        if (v != 0 && !enabled)
        {
            digitalWrite(PIN_TMC_EN, LOW);
            enabled = true;
        }
        if (tmc && v != lastV)
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        }
        if (v == 0 && enabled && now - stopAt >= IDLE_OFF_MS)
        {
            digitalWrite(PIN_TMC_EN, HIGH);
            enabled = false;
        }
        HwBusUnlock();
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
void HwBegin()
{
    pinMode(PIN_TMC_EN, OUTPUT);                    // motor off first thing
    digitalWrite(PIN_TMC_EN, HIGH);
    pinMode(PIN_TMC_STEP, OUTPUT);
    digitalWrite(PIN_TMC_STEP, LOW);
    pinMode(PIN_TMC_DIR, OUTPUT);
    digitalWrite(PIN_TMC_DIR, LOW);
    pinMode(PIN_TMC_DIAG, INPUT);

    FansBegin();
    Ds18b20Begin(PIN_TEMP_OUT);
#if AUDIO_MODE && MIC_INMP441
    analogReadResolution(12);                       // the ADC stays free: the 12 V sense reads one-shot
    if (!SoundStreamBeginI2s(PIN_I2S_SCK, PIN_I2S_WS, PIN_I2S_SD, PIN_MIC))  // GPIO 3, if JP2 joins it, left floating
        Log("Microphone: the I2S driver didn't start");
#elif AUDIO_MODE
    if (!SoundStreamBegin(PIN_MIC, PIN_MIC_LINK, PIN_12V_SENSE))    // it also reads the 12 V sense
        Log("Microphone: the ADC's continuous mode didn't start");
#else
    analogReadResolution(12);
    Ds18b20Begin(PIN_TEMP_IN);
#endif

    Serial1.begin(TMC_UART_BAUD, SERIAL_8N1, PIN_TMC_RX, PIN_TMC_TX);
    Wire.begin(PIN_SCD_SDA, PIN_SCD_SCL, SCD_I2C_HZ);
    Wire1.begin(PIN_ENC_SDA, PIN_ENC_SCL, ENC_I2C_HZ);
    Wire.setTimeOut(50);
    Wire1.setTimeOut(20);
    Scd40Begin(&Wire);
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
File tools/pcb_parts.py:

"""Parts and nets of the controller PCB (pcb/window_vent_ctrl*), shared by tools/pcb_schematic.py and tools/pcb_layout.py.

The circuit is the one in firmware/images/wiring.svg and doc/perfboard.svg; pins as in firmware/libs/WindowVent/src/Pins.h.
Each part: reference, lib_id (KiCad symbol), value, footprint, {pin number: net}. Pins left out are not connected.

Two boards, chosen with the VENT_PCB environment variable (the same for every pcb_*.py script):
  lite     pcb/window_vent_ctrl (v1.5): the Freenove ESP32-S3 Lite (FNK0099), 2 x 20 pins
  devkitc  (default) pcb/window_vent_ctrl_devkitc (v2.0): an ESP32-S3-N16R8 board in the DevKitC-1 layout, 2 x 22
           pins, with a U.FL connector for an external antenna. Its 20 middle pins of each row are the Freenove's, on the
           same holes; the extra pin at each end is 3V3 or GND. No JP1 (D1 bypass): the extra pins take its place. No TP3
           (VIN) and TP4 (12V): C2 and J1 take their place; probe J1 pin 1 (VIN) or a fan header's pin 2 (12V).
"""
import os

VARIANT = os.environ.get("VENT_PCB", "devkitc")
assert VARIANT in ("lite", "devkitc"), "VENT_PCB: lite or devkitc"
DEVKITC = VARIANT == "devkitc"
NAME = "window_vent_ctrl_devkitc" if DEVKITC else "window_vent_ctrl"
REV = "v2.0" if DEVKITC else "v1.5"

ESP_L = ["3V3", "EN", "4", "5", "6", "7", "15", "16", "17", "18", "8", "3", "46", "9", "10", "11", "12", "13", "14", "5V"]
ESP_R = ["TX", "RX", "1", "2", "42", "41", "40", "39", "38", "37", "36", "35", "0", "45", "48", "47", "21", "20", "19", "GND"]
if DEVKITC:                                            # one more pin at each end of each row
    ESP_L = ["3V3"] + ESP_L + ["GND"]
    ESP_R = ["GND"] + ESP_R + ["GND"]
TMC_S = ["EN", "MS1", "MS2", "PDN", "UART", "CLK", "STEP", "DIR"]
TMC_P = ["VM", "GND", "M1B", "M1A", "M2A", "M2B", "VIO", "GND"]

# ESP32-S3 GPIO -> net (the rest of its pins stay free)
ESP_GPIO = {
    "4": "FAN0_PWM", "5": "FAN1_PWM", "6": "ENC_SDA", "7": "ENC_SCL", "15": "FAN0_TACH", "16": "FAN1_TACH",
    "17": "TMC_TX", "18": "TMC_UART", "8": "SCD_SDA", "9": "SCD_SCL", "10": "TMC_EN", "11": "TMC_STEP",
    "12": "TMC_DIR", "13": "TMC_DIAG", "14": "DQ_OUT", "1": "V12_SENSE", "21": "DQ_IN", "3": "MIC", "38": "I2S_SCK", "39": "I2S_WS",
}


def esp_nets():
    nets = {}
    for i, name in enumerate(ESP_L + ESP_R, 1):
        if name == "3V3":
            nets[str(i)] = "+3V3"
        elif name == "GND":
            nets[str(i)] = "GND"
        elif name in ESP_GPIO:
            nets[str(i)] = ESP_GPIO[name]
    return nets


TMC_NETS = {"1": "TMC_EN", "2": "GND", "3": "GND", "4": "TMC_PIN4", "5": "TMC_PIN5", "7": "TMC_STEP", "8": "TMC_DIR",
            "9": "+12V", "10": "GND", "11": "MOT_1B", "12": "MOT_1A", "13": "MOT_2A", "14": "MOT_2B",
            "15": "+3V3", "16": "GND"}

R_FLAT = "window_vent:R_DIN0207_P10.16mm_Flat_Tight"   # lying under the modules' edges (courtyard = body)
R_UP = "Resistor_THT:R_Axial_DIN0207_L6.3mm_D2.5mm_P2.54mm_Vertical"
R_0402 = "Resistor_SMD:R_0402_1005Metric_Pad0.72x0.64mm_HandSolder"   # the jumpers: a 0 ohm 0402 or a short wire
DNP = {"JP2"}                                          # left out unless needed (the audio mode)


def hdr(n):
    return f"Connector_PinHeader_2.54mm:PinHeader_1x{n:02d}_P2.54mm_Vertical"


PARTS = [
    # ref, lib_id, value, footprint, pins, description (for the schematic)
    ("U1", "window_vent:ESP32S3_DevKitC", "ESP32-S3-N16R8 (DevKitC-1 type)", "window_vent:ESP32S3_DevKitC_N16R8", esp_nets(), "")
    if DEVKITC else
    ("U1", "window_vent:ESP32S3_Lite", "Freenove ESP32-S3 Lite", "window_vent:Freenove_ESP32S3_Lite", esp_nets(), ""),
    ("U2", "window_vent:TMC2209_Module", "TMC2209 module", "window_vent:TMC2209_StepStick", TMC_NETS, ""),
    ("J1", "Connector_Generic:Conn_01x02", "12V IN", hdr(2), {"1": "VIN", "2": "GND"}, ""),
    ("JP1", "Jumper:Jumper_2_Open", "D1 bypass", hdr(2), {"1": "VIN", "2": "+12V"}, ""),
    # audio mode: a microphone on J7 instead of the indoor probe; GPIO 21 has no ADC, so JP2 joins it to GPIO 3 (ADC1)
    ("JP2", "Jumper:Jumper_2_Open", "0R AUDIO", R_0402, {"1": "DQ_IN", "2": "MIC"}, ""),
    # the driver's PDN_UART: on pin 5 (UART) or pin 4 (PDN) depending on the module, so both are fitted by default;
    # leave one out if a module uses that pin for something else
    ("JP3", "Jumper:Jumper_2_Bridged", "0R PDN", R_0402, {"1": "TMC_UART", "2": "TMC_PIN4"}, ""),
    ("JP4", "Jumper:Jumper_2_Bridged", "0R UART", R_0402, {"1": "TMC_UART", "2": "TMC_PIN5"}, ""),
    ("D1", "Device:D_Schottky", "1N5822", "Diode_THT:D_DO-201AD_P5.08mm_Vertical_AnodeUp", {"1": "+12V", "2": "VIN"}, ""),
    ("C1", "Device:C_Polarized", "220uF 50V", "Capacitor_THT:CP_Radial_D10.0mm_P5.00mm", {"1": "+12V", "2": "GND"}, ""),
    ("R1", "Device:R", "10k", R_UP, {"1": "FAN0_TACH", "2": "+3V3"}, ""),
    ("R2", "Device:R", "10k", R_UP, {"1": "FAN0_PWM", "2": "GND"}, ""),
    ("R3", "Device:R", "10k", R_UP, {"1": "FAN1_TACH", "2": "+3V3"}, ""),
    ("R4", "Device:R", "10k", R_UP, {"1": "FAN1_PWM", "2": "GND"}, ""),
    ("R5", "Device:R", "10k", R_FLAT, {"1": "TMC_EN", "2": "+3V3"}, ""),
    ("R6", "Device:R", "1k", R_FLAT, {"1": "TMC_TX", "2": "TMC_UART"}, ""),
    ("R7", "Device:R", "100k", R_FLAT, {"1": "+12V", "2": "V12_SENSE"}, ""),
    ("R8", "Device:R", "22k", R_FLAT, {"1": "V12_SENSE", "2": "GND"}, ""),
    ("R9", "Device:R", "4.7k", R_FLAT, {"1": "DQ_IN", "2": "+3V3"}, ""),
    ("R10", "Device:R", "4.7k", R_FLAT, {"1": "DQ_OUT", "2": "+3V3"}, ""),
    ("J2", "Connector_Generic:Conn_01x04", "FAN 0 exhaust", hdr(4), {"1": "GND", "2": "+12V", "3": "FAN0_TACH", "4": "FAN0_PWM"}, ""),
    ("J3", "Connector_Generic:Conn_01x04", "FAN 1 intake", hdr(4), {"1": "GND", "2": "+12V", "3": "FAN1_TACH", "4": "FAN1_PWM"}, ""),
    ("J4", "Connector_Generic:Conn_01x04", "MOTOR", hdr(4), {"1": "MOT_1A", "2": "MOT_1B", "3": "MOT_2A", "4": "MOT_2B"}, ""),
    ("J5", "Connector_Generic:Conn_01x04", "SCD40", hdr(4),   # 1:1 with the SCD40 module: GND, VDD, SCL, SDA
     {"1": "GND", "2": "+3V3", "3": "SCD_SCL", "4": "SCD_SDA"}, ""),
    ("J6", "Connector_Generic:Conn_01x04", "AS5600", hdr(4), {"1": "+3V3", "2": "GND", "3": "ENC_SDA", "4": "ENC_SCL"}, ""),
    # J7 (2 x 3): the indoor DS18B20 or the MAX9814 on its first row (3V3, IN, GND, as the old 3-pin header), or the
    # INMP441 (I2S) on both rows: SD on IN (GPIO 21), WS, SCK, and the second GND for its L/R pin
    ("J7", "Connector_Generic:Conn_02x03_Odd_Even", "DS18B20 in / MIC", "Connector_PinHeader_2.54mm:PinHeader_2x03_P2.54mm_Vertical",
     {"5": "+3V3", "3": "DQ_IN", "1": "GND", "6": "I2S_WS", "4": "I2S_SCK", "2": "GND"}, ""),
    ("J8", "Connector_Generic:Conn_01x03", "DS18B20 out", hdr(3), {"1": "GND", "2": "DQ_OUT", "3": "+3V3"}, ""),
    # +3V3 bulk capacitor (6.3 x 11 mm): its pads are also the 3V3 and GND test points
    ("C2", "Device:C_Polarized", "470uF 10V", "Capacitor_THT:CP_Radial_D6.3mm_P2.50mm", {"1": "+3V3", "2": "GND"}, ""),
    ("TP3", "Connector:TestPoint", "VIN", "TestPoint:TestPoint_THTPad_D2.0mm_Drill1.0mm", {"1": "VIN"}, ""),
    ("TP4", "Connector:TestPoint", "12V", "TestPoint:TestPoint_THTPad_D2.0mm_Drill1.0mm", {"1": "+12V"}, ""),
    ("TP5", "Connector:TestPoint", "DIAG", "TestPoint:TestPoint_THTPad_D2.0mm_Drill1.0mm", {"1": "TMC_DIAG"}, ""),
    ("H1", "Mechanical:MountingHole", "M2", "MountingHole:MountingHole_2.2mm_M2", {}, ""),
    ("H2", "Mechanical:MountingHole", "M2", "MountingHole:MountingHole_2.2mm_M2", {}, ""),
    ("H3", "Mechanical:MountingHole", "M2", "MountingHole:MountingHole_2.2mm_M2", {}, ""),
    ("H4", "Mechanical:MountingHole", "M2", "MountingHole:MountingHole_2.2mm_M2", {}, ""),
]
if DEVKITC:
    PARTS = [p for p in PARTS if p[0] not in ("JP1", "TP3", "TP4")]
    # D1 with a tight courtyard (tools/pcb_layout.py): C2 stands next to its anode lead
    PARTS = [p[:3] + ("window_vent:D_DO-201AD_P5.08mm_Vertical_AnodeUp_Tight",) + p[4:] if p[0] == "D1" else p for p in PARTS]

POWER_NETS = {"GND": "power:GND", "+3V3": "power:+3V3", "+12V": "power:+12V"}

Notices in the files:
README.md:
License:
Copyright (c) 2026 Marc-Antoine Massicotte.
This design (CAD model, STL files, images, documentation and scripts) is released under the [CERN Open Hardware Licence Version 2 - Permissive](LICENSE) (CERN-OHL-P-2.0). You may use, modify, make, share and sell it freely, as long as you keep this notice. It comes with no warranty of any kind, and the author accepts no liability for its use.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
